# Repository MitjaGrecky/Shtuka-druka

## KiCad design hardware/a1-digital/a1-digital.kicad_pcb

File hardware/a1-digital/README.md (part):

# A1 - Digital audio board (under the slope, left; mates R1 at a right angle)

> *Outdated as a heading (audit 26.11.2026): current rev 1.1, see Status below and the Rev sections at the end; the rev 0.6 block is history.*
>
> **Rev 0.6 (18.11.2026, решение главного инженера, P108):** конденсаторы связи — по одному неполярному Würth WCAP-ASNP 865250349007 (47 мкФ 16 В, Ø8×6,5, LCSC C5530373) на канал, 40 шт., паять вручную (на JLC нет в наличии, Digikey 239 шт.). THD+N на 20–100 Гц замерить на первой плате. Rev 0.5 с парами FVH016 не заказывать.

20 differential ADC channels, 8 DAC channels, two XMOS xcore.ai, USB isolation, two clock sources, quiet supplies.
Plan, pinouts and sources: `PLAN.md`. Decisions: R82-R84 (two USB ports, TDM, 96 kHz hardware), R87 (volume in the DAC), R88 (two spare
channels), R114 (two oscillators), R116/R117 (converters, two paths per mic), R136 (CS4308P, current outputs).

**Status: rev 1.1 (25.11.2026) - placed board, not routed, pin rule (A-037) not yet applied; USB isolator TI ISOUSB211 since rev 0.9 (see the Rev sections at the end; rev 0.6 text below kept as history: 613 parts, 18.11.2026).** Schematic checked against the datasheets (cloud task #26, rev 0.2): CS4308P DS1317, CS53A04P DS1397
(same family as the CS5304P/8P - the CS5308P/CS5304P datasheets themselves were not reachable), XU316-1024-QF60B, ADuM4165/4166, SiTime/SCTF oscillators.

## Blocks

| Block | Parts | Notes |
|---|---|---|
| ADC | 2 x CS5308P (8 ch, C42457798) + 1 x CS5304P (4 ch, C49192888) | SPI software mode (CONFIG1 to VDD_A), ASP secondary, TDM out on DOUT1. Chip A = ADC 1-8 (mic 1-2 two paths, Hi-Z 1-2 two paths), B = ADC 9-16 (phono 2, line 1-6), C = ADC 17-20 (line 7-8, spare 1-2) |
| ADC input buffers | 20 x OPA1656 dual, 47 uF X5R (2.8 Hz) + 1.2k in, 300 R + 680 pF feedback, 10 R out, 15 nF across the pair | Cirrus circuit, gain 1/4: R1 delivers 8 Vrms diff FS -> 2 Vrms at the pins (AN0635); inverting, so the source P leg goes to the N pin (polarity kept); non-inverting inputs at ADC_VMID |
| DAC | CS4308P (8 ch) | Current outputs: 8 x OPA1656 dual I-V, Rf 1.2k + 620 pF per leg (AN0679), 47 R build-out, 1 nF across. Outputs 1-4 Main L/R, Aux L/R -> R1; 5-8 Phones 1 L/R, 2 L/R -> F1. Not in the EasyEDA library (R136) |
| xcore A (U) | XU316-1024-QF60B (C7397517), W25Q32JVSSIQ boot flash (4 MB, B18; C82344) | TDM master (BCLK, FSYNC, DAC data, 3 ADC data), SPI to the 4 converters (tile 1), converter reset, oscillator enables, USB port A from the R2 hub, XLINK0 to B |
| xcore B | XU316-1024-QF60B, W25Q16 | USB port B to the external computer through the ISOUSB211 (rev 0.9; was ADuM4166), PDM microphone (header), XLINK0 to A |
| USB isolator | TI ISOUSB211DPR (C5772877, rev 0.9; was ADuM4166 C5367256), USBLC6 on the computer side, Rd 5.1k | Computer side on the isolated ground GNDPC; the rear USB-C (PC) receptacle on the wall comes in over a JST PH 6 cable (R145: data only) |
| Clocks | 24.576 MHz and 22.5792 MHz oscillators with enable pins (parts to choose), 33 R each into MCLK, 22 R star to every load | Default 48 kHz family on; xcore A can switch (R114). 24 MHz crystals for both xcore cores |
| Supplies | +3V3A TPS7A4701 (ANY-OUT 3.3 V), +3V3D and +1V8 AP2112K, +0V9 x 2 TLV62568 (0.6 V x 1.5) from +5V; +-12 V from R1 for the op-amps | +-12 V and +5 V arrive through the R1 board-to-board connector (PW -> R1 -> A1) |

## Connectors

| J | To | Notes |
|---|---|---|
| 2x20 socket | R1 "to A1 (ADC 1-10)" | same pinout; pairs on adjacent pins with a GND pair between |
| 2x25 socket | R1 "to A1 (ADC 11-18, DAC 1-4, power)" | same pinout; +12V, -12V, +5V x 2 on pins 47-50 |
| 2x6 header | F1 "from A1" | Phones 1 and 2 pairs, twisted |
| JST PH 4 | R2 hub "USB down: A1 port A" | VBUS sense only |
| JST PH 6 | rear USB-C (PC) | PC_VBUS, DM, DP, CC1, CC2, GNDPC |
| JST PH 6 | spare ADC 19-20 | R88 |
| JST PH 6 x 2 | JTAG A and B (1.8 V logic) | xTAG adapter - check the pinout |
| JST PH 4 | PDM microphone | CLK, DATA, +3V3D, GND |

xcore pin plan (as in `gen/design.py`): A: MCLK X0D11, BCLK X0D00, FSYNC X0D35, DAC data X0D36, ADC data X0D37/38/39; SPI SCK X1D00,
MOSI X1D01, MISO X1D10, CS X1D11/X1D22/X1D13/X1D34; reset X0D29; oscillator enables X0D30/X0D31; hub VBUS sense X0D40; XLINK0 X1D16-X1D19.
B: MCLK X0D11, PDM X1D00/X1D01. QSPI boot on X0D01 (SS), X0D10 (SCLK), X0D04-07.

## Checked (cloud task #26, rev 0.2)

**Converters (CS4308P, CS53A04P family).** Pin maps of the CS4308P (all 48) and of the four-channel ADC half (supplies, SPI, ASP, CONFIG, IN1-4) agree with the schematic.
- Capacitors as in the typical-connection drawings: VDD_A1 and VDD_A2 each 4.7 uF + 10 nF, LDO_A_FILT 1 uF, LDO_D_FILT 1 uF with VDD_D tied to it (no separate cap),
  VDD_IO 0.1 uF. Rev 0.1 had 1 uF / 10 uF / 4.7 uF.
- DAC: DAC_FILTP 22 uF to **VDD_A2**, DAC_FILTN 22 uF to ground (rev 0.1: 4.7 uF between them), DAC_VMID 10 uF (rev 0.1: 1 uF).
  ADC: FILT 4.7 uF + 0.47 uF (the figure text is ambiguous between 0.47/4.7 and 0.22/2.2; VMID 2.2 uF + 0.22 uF), ADC_FILTP through 1 R to VDD_A.
- SPI mode: CONFIG1 0 R to VDD_A, **CONFIG5 to ground**; in software mode CONFIG2-4 of the ADC are the **HGC SPI outputs** (clock, data, chip select for external
  preamplifiers, off by default): 1 k to ground instead of 10 k. DAC CONFIG2-4 unused to ground.
- No power-up sequencing; RESET low >= 1 ms, control port ready 5 ms after the release; POR of VDD_A 1.9-2.7 V.
- MCLK 24.576 / 22.5792 MHz directly (software mode, PLL bypass) or 512 fs with the PLL, +-1 %, duty 40-60 %. **ASP secondary: MCLK, BCLK and FSYNC must come from a
  common source** - here MCLK from the oscillator and BCLK / FSYNC derived by xcore A from the same MCLK (lib_xua master mode does that).
- ADC input: 0 dBFS = 2.0 Vrms differential at the pins (scales with VDD_A), input resistance 3 kOhm differential in the default mode (INxx_HIZ = 0).
- **Coupling capacitors 68 uF -> 47 uF X5R 10 V (1210)**: a 68 uF 25 V ceramic does not exist, and a polarised one cannot be used - the buffer side sits at 1.6 V
  while each leg swings +-5.7 V at full scale (reverse voltage). Corner 2.8 Hz instead of 1.95 Hz; the capacitor voltage never exceeds 7.3 V. 20 x 2 = 40 pieces (rev 0.6: non-polar Würth WCAP-ASNP instead of X5R).
- CS4308P: **no LCSC number** (a new part; Digikey CS4308P-DNR, 16 weeks lead time, 48-QFN 6x6, 0.4 mm). Footprint body 6x6 and pitch 0.4 are confirmed;
  the exposed-pad size is in section 10 of the datasheet (not retrievable here) - draw the footprint from it. Output: 1.67 mA rms per channel, 1.2 kOhm = 2.0 Vrms (AN0679).

**XU316-1024-QF60B.**
- Pin map of the supplies and of all used ports agrees (VDD x 8 + paddles 61-64 at 0.9 V, VDDIOL/R/T 3.3 V, VDDIOB18 x 2 1.8 V, USB_VDD33 3.3 V, USB_VDD18 1.8 V).
  Bottom bank (XIN, XOUT, RST_N, JTAG) is 1.8 V only - correct.
- **PLL_AVDD:** 0.9 V nominal, filter = ferrite bead 600 R at 100 MHz (DCR < 1 R) + **1 uF** MLCC at the pin (rev 0.1: 4.7 uF + 100 nF kept as a second capacitor).
- **Sequencing:** VDD and VDDIO within about 50 ms, monotonic; the 3.3 V domains must be valid before reset is released, and VDDIOB18 must not be last - here all rails come from the
  same +5 V and the TLV62568 / AP2112K start together; RST_N has a 100 nF to ground with the 10 k pull-up to 1.8 V (about 1 ms delay), which keeps it low while the rails rise.
- Crystal 24 MHz, 12 pF load, ESR <= 60 R, tolerance +-500 ppm or better: C70590 with 18 pF caps is right.
- **USB PHY:** enable it on **tile 0** (xcore A and B). The USB ports of the PHY are not on the QF60 pins of tile 0; enabling it on **tile 1 removes ports 1F (X1D13) and 1K (X1D34) -
  our SPI chip selects CS_ADCC and CS_DAC of xcore A would be lost.** lib_xua then runs the USB and the audio on tile 0 (supported); the SPI to the converters and the PDM microphone stay on tile 1.
- Boot: X0D04-X0D06 are sampled after reset with weak pull-downs, 000 = QSPI; the flash must answer a Quad I/O read (0xEB) within 300 us, so its QE bit must be set (the first programming
  goes over JTAG with xflash, which sets it). A blank W25Q16 may pull IO2/IO3 up internally; if the board does not boot before the first programming, program it over JTAG.
- Flash: the datasheet gives no minimum; a lib_xua UAC2 application with DFU needs about 2x the image, so the user chose 4 MB (B18): W25Q32JVSSIQ (C82344), same package and pinout.
- Ports: BCLK X0D00 (1A), MCLK X0D11 (1D), FSYNC X0D35, DAC data X0D36, ADC data X0D37-39 are all 1-bit ports of tile 0 (nine 1-bit ports on tile 0: 1A, 1B, 1C, 1D, 1L-1P);
  SPI on tile 1 (1A, 1B, 1C, 1D, 1F, 1G, 1K). Everything the plan uses exists. TDM master with a 1-bit BCLK clock port is the lib_xua configuration; PDM needs a 1-bit data port (X1D01).

**ADuM4166** (pin table: all 20 agree).
- **VBUS2 was +5 V with VDD2 on the external 3.3 V: the internal LDO would fight our regulator** (and VDD1/VDD2 need exactly 0.1 uF with the LDO). Now VBUS2 = VDD2 = +3V3D (LDO bypassed, 3.0-3.6 V),
  VDD2 / VBUS2 0.1 uF, VDD1 0.1 uF (LDO output, **not** 1 uF: "above 0.1 uF disrupts the start-up"), VBUS1 0.1 uF; PGOOD open. VBUS1 = PC VBUS 3.0-5.5 V.
- Crystal 24 MHz, <= 50 ppm and <= 100 ppm stability, starts within 0.3 ms, typical load 10 pF: C70590 (12 pF) with 15 pF caps (about 10.5 pF) works; a 10 pF part is better. *(Outdated, P122: this is the ADuM4166 isolator crystal, gone in rev 0.9; the xcore crystal X322524MOB4SI uses 18 pF caps per the generator.)* Or a 24 MHz clock into XI2 (XO2 open).
- Footprint: LCSC lists it as SOIC-20-300mil (rev 0.1 had a 15.4 mm body "per the LCSC part" - a 300-mil SOIC-20 is 12.8 mm): check against the datasheet drawing; the LCSC number of the BRIZ-RL
  is C5581725 (out of stock on 14.11.2026, $15), the schematic carries C5367256 from the PC - check which one is the stocked variant.

**Oscillators** (R114; actual parts by the generator, P122): Y1 24.576 MHz SCTF SX3M24.576B10F20TNN (C7431342), Y2 22.5792 MHz SCTF SX3M22.5792B10F20TNN (C7431341), both 3.3 V CMOS, +-10 ppm, pin 1 tri-state; SiTime SiT8208AI-21-33E-24.576000 (C839665, 0.5 ps; **out of stock** on 14.11) is only the spare (В19). Earlier text (rev 0.2-0.5; SX3M22.5792M20F30TNN C2901572 and SiT8208 as the main part are outdated): Pin 1 = enable, high = on, as the schematic assumes. For a 123 dB ADC the clock jitter matters: SiTime
has 0.5 ps; the SCTF part must be checked or replaced (SiT8208 22.5792). *(Outdated, P122: SX3M is the accepted main part, SiT8208 is the spare; jitter is measured on the first board, B19.)* The 33 R + 22 R star is kept.

**Supplies.** TPS7A4701: ANY-OUT 1.4 + 1.6 + 0.2 + 0.1 = 3.3 V with pins 8 (1.6 V), 11 (0.2 V), 12 (0.1 V) to ground - confirmed from the symbol; NR/SS 1 uF not verified (TI text not retrievable).
AP2112K 3.3 V: 600 mA max, estimated 150 mA typical -> 0.26 W in a SOT-23-5 (250 K/W = +65 K): **warm, keep an eye on it on the first board** - the analog side is not on this regulator
(it is on the TPS7A4701). TLV62568 0.9 V x 2: 1 A, the feedback 0.6 x (1 + 100k / 200k) = 0.9 V is right; the xcore.ai core draws about 0.5 A at full load (to measure).

## Still open

- CS5308P and CS5304P datasheets (pins 12-22 of the CS5304P are DNC in the CS53A04P; the CS5308P has pins 13-22 as IN5-8 and the second VMID/FILT) - compare once the datasheet is available.
- Exposed-pad size of the CS4308P footprint; body length of the ADuM4166; CS4308P order.
- Oscillator parts (stock), 10 pF crystal for the ADuM4166.
- AP2112K temperature.

Checks: `tools/sch_netcheck.py hardware/a1-digital` - 663 symbol units, 1887 pins, 0 mismatches; every symbol pin listed. ERC by CI.
Symbols for the CS5308P / CS5304P / CS4308P / XU316 / ADuM4166: `hardware/common/gen/ic_symbols.py` -> `ShtukaDruka.kicad_sym`; footprint of
the XU316: `ShtukaDruka.pretty` (converted from the LCSC library with `tools/eda/lcsc_fp.py`).

Generators: `gen/design.py`, `gen/make_sch.py`. On the PC set `KICAD_SYMBOL_DIR=<repo>/hardware/common/sym7`.

License: CERN-OHL-S-2.0 (hardware), AGPL-3.0-or-later (scripts).

## Rev 0.3: placed board for routing (14.11.2026, PC)
Placed board (no routing) generated by `gen/make_pcb.py`; `UNROUTED` marker for CI; package `hardware/for-routing/A1`. Placement is a starting point: the rest by `hardware/common/gen/autoplace.py` (ICs on a grid, small parts around the IC they share signals with, cable headers along the bottom edge). Outline and mounting holes are rough until the enclosure is fixed. `pcb_geomcheck`: 0 problems.

Low case (17.11.2026, R162): the board stands on a 2 mm tray over the battery. Parts on the bottom side reach 7.7 mm (5 x CP 6.3 x 7.7), so the standoffs between the board and the tray must be >= 8.5 mm, with an insulating film on the tray. Socket rows of J1 / J2 end up about 30.4 / 32.9 mm above the floor (superseded: A1 now stands on the floor, R174; header height of R1 J4 / J5: R1 rev 0.7).

Rev 0.5 (17.11.2026, R172): 80 x FVH016 electrolytics in back-to-back pairs instead of the X5R capacitors; **superseded by rev 0.6 (P108), do not order rev 0.5**: the reverse-voltage rating of the pair was never confirmed (up to about +-2.8 V on each capacitor at 20 Hz and full scale).

Rev 0.6 (18.11.2026): 80 FVH016 заменены 40 одиночными WCAP-ASNP (47 мкФ, угол ≈ 2,8 Гц с 1,2 к). 613 деталей, 0 несовпадений нетлиста, 0 перекрытий. Footprint CP_Elec_8x6.5 приблизителен к даташиту.

## Rev 0.5: ADC overload clamps (audit 18.11.2026)
CS5308P DS1314F2 table 3-3: analog inputs -0.3 ... VDD_A + 0.3 V, +-10 mA. A clipped R1 stage leaves the buffer at -1.1 ... +4.4 V (about 70 mA through 10 R into the ADC diodes). One **BAT54S** (onsemi C19726, Schottky pair to +3V3A / GND) per ADC pin: 40 parts, near the pins. Stock: the CS5308P itself has 0 pcs at JLC on 18.11.2026 (Digikey or direct from Cirrus).

## Rev 0.6: 24.576 MHz oscillator (18.11.2026)
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
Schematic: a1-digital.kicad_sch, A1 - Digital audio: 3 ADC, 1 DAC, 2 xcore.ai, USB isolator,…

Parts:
C1, C3, C5, C22, C23, C37, C38, C52, C53, C203, C204, C258, C274: 1u; C_0603_1608Metric
C2, C4, C28, C30, C43, C45, C56: 2.2u; C_0603_1608Metric
C6, C9, C12, C207: 10u; C_0805_2012Metric
C7, C10, C11, C13, C14, C205, C206: 22u; C_0805_2012Metric
C8, C15, C16, C21, C36, C51, C202, C248, C249, C250, C251, C253, C254, C255, C256, C257, C259, C262, C263, C264, C265, C266, C267, C269, C270, C271, C272, C273, C275, C278, C279, C281, C283, C286, C288: 100n; C_0402_1005Metric
C17, C19, C24, C26, C32, C34, C39, C41, C47, C49, C54, C198, C200: 4.7u; C_0805_2012Metric
C18, C20, C33, C35, C48, C50, C199, C201, C284, C289: 10n; C_0402_1005Metric
C25, C27, C40, C42, C55: 470n; C_0402_1005Metric
C29, C31, C44, C46, C57: 220n; C_0402_1005Metric
C58, C59, C65, C66, C72, C73, C79, C80, C86, C87, C93, C94, C100, C101, C107, C108, C114, C115, C121, C122, C128, C129, C135, C136, C142, C143, C149, C150, C156, C157, C163, C164, C170, C171, C177, C178, C184, C185, C191, C192, C208, C209, C213, C214, C218, C219, C223, C224, C228, C229, C233, C234, C238, C239, C243, C244: 100n 25V; C_0603_1608Metric
C60, C62, C67, C69, C74, C76, C81, C83, C88, C90, C95, C97, C102, C104, C109, C111, C116, C118, C123, C125, C130, C132, C137, C139, C144, C146, C151, C153, C158, C160, C165, C167, C172, C174, C179, C181, C186, C188, C193, C195: 47u 16V NP; CP_Elec_8x6.5; LCSC C5530373
C61, C63, C68, C70, C75, C77, C82, C84, C89, C91, C96, C98, C103, C105, C110, C112, C117, C119, C124, C126, C131, C133, C138, C140, C145, C147, C152, C154, C159, C161, C166, C168, C173, C175, C180, C182, C187, C189, C194, C196: 680p C0G; C_0603_1608Metric
C64, C71, C78, C85, C92, C99, C106, C113, C120, C127, C134, C141, C148, C155, C162, C169, C176, C183, C190, C197: 15n C0G; C_0603_1608Metric
C210, C211, C215, C216, C220, C221, C225, C226, C230, C231, C235, C236, C240, C241, C245, C246: 620p C0G; C_0603_1608Metric
C212, C217, C222, C227, C232, C237, C242, C247: 1n C0G; C_0603_1608Metric
C252, C268: 4.7u; C_0603_1608Metric
C260, C261, C276, C277: 18p; C_0402_1005Metric
C280, C285: 1u; C_0402_1005Metric
C282, C287: 2.2u; C_0402_1005Metric
C290, C291, C292, C293, C294: 47u 25V; CP_Elec_6.3x7.7; LCSC C190223
D1, D2, D3, D4, D5, D6, D7, D8, D9, D10, D11, D12, D13, D14, D15, D16, D17, D18, D19, D20, D21, D22, D23, D24, D25, D26, D27, D28, D29, D30, D31, D32, D33, D34, D35, D36, D37, D38, D39, D40: BAT54S; SOT-23; LCSC C19726
FB1, FB2: 600R; R_0603_1608Metric; LCSC C14709
H1, H2, H3, H4, H5, H6: M3; MountingHole_3.2mm_M3_ISO7380
J1: from R1 (ADC 1-10); PinSocket_2x20_P2.54mm_Horizontal
J2: R1 (ADC 11-18, DAC 1-4, power); PinSocket_2x25_P2.54mm_Horizontal
J3: to F1; PinHeader_2x06_P2.54mm_Vertical
J4: USB port A (hub); JST_PH_B4B-PH-K_1x04_P2.00mm_Vertical; LCSC C131334
J5: USB-C PC; JST_PH_B6B-PH-K_1x06_P2.00mm_Vertical; LCSC C131342
J6: spare ADC 19-20; JST_PH_B6B-PH-K_1x06_P2.00mm_Vertical; LCSC C131342
J7: PDM mic; JST_PH_B4B-PH-K_1x04_P2.00mm_Vertical; LCSC C131334
J8: JTAG A; JST_PH_B6B-PH-K_1x06_P2.00mm_Vertical; LCSC C131342
J9: JTAG B; JST_PH_B6B-PH-K_1x06_P2.00mm_Vertical; LCSC C131342
L1, L2: 2.2uH; L_Bourns-SRN4018
R1, R3, R10, R20, R30, R44, R45, R52, R53, R60, R61, R68, R69, R76, R77, R84, R85, R92, R93, R100, R101, R108, R109, R116, R117, R124, R125, R132, R133, R140, R141, R148, R149, R156, R157, R164, R165, R172, R173, R180, R181, R188, R189, R196, R197, R199, R250, R251, R252, R253, R254, R255, R256: 100k; R_0402_1005Metric
R2, R4: 200k; R_0402_1005Metric
R5, R7, R16, R26, R36, R202, R203, R204, R205, R239, R240, R242, R243, R244: 10k; R_0402_1005Metric
R6, R8, R11, R21, R31, R200: 33; R_0402_1005Metric
R9, R19, R29, R198, R238, R241, R248, R249: 22; R_0402_1005Metric
R12, R22, R32, R201: 0; R_0402_1005Metric
R13, R14, R15, R23, R24, R25, R33, R34, R35: 1k; R_0402_1005Metric
R17, R18, R27, R28, R37: 1; R_0402_1005Metric
R38, R41, R46, R49, R54, R57, R62, R65, R70, R73, R78, R81, R86, R89, R94, R97, R102, R105, R110, R113, R118, R121, R126, R129, R134, R137, R142, R145, R150, R153, R158, R161, R166, R169, R174, R177, R182, R185, R190, R193, R206, R208, R210, R212, R214, R216, R218, R220, R222, R224, R226, R228, R230, R232, R234, R236: 1.2k; R_0402_1005Metric
R39, R42, R47, R50, R55, R58, R63, R66, R71, R74, R79, R82, R87, R90, R95, R98, R103, R106, R111, R114, R119, R122, R127, R130, R135, R138, R143, R146, R151, R154, R159, R162, R167, R170, R175, R178, R183, R186, R191, R194: 300; R_0402_1005Metric
R40, R43, R48, R51, R56, R59, R64, R67, R72, R75, R80, R83, R88, R91, R96, R99, R104, R107, R112, R115, R120, R123, R128, R131, R136, R139, R144, R147, R152, R155, R160, R163, R168, R171, R176, R179, R184, R187, R192, R195: 10; R_0402_1005Metric
R207, R209, R211, R213, R215, R217, R219, R221, R223, R225, R227, R229, R231, R233, R235, R237: 47; R_0603_1608Metric
R245: 20k; R_0402_1005Metric
R246, R247: 5.1k; R_0402_1005Metric
U1: AP2112K-3.3; SOT-23-5; LCSC C51118
U2: AP2112K-1.8; SOT-23-5; LCSC C176944
U3: TPS7A4701; Texas_RGW0020A_VQFN-20-1EP_5x5mm_P0.65mm_EP3.15x3.15mm_Ther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; LCSC C90084
U4, U5: TLV62568; SOT-23-5; LCSC C163219
U6, U7: CS5308P; QFN-48-1EP_6x6mm_P0.4mm_EP4.6x4.6mm; LCSC C42457798
U8: CS5304P; QFN-48-1EP_6x6mm_P0.4mm_EP4.6x4.6mm; LCSC C49192888
U9, U10, U11, U12, U13, U14, U15, U16, U17, U18, U19, U20, U21, U22, U23, U24, U25, U26, U27, U28, U30, U31, U32, U33, U34, U35, U36, U37: OPA1656; SOIC-8_3.9x4.9mm_P1.27mm; LCSC C1849431
U29: CS4308P; QFN-48-1EP_6x6mm_P0.4mm_EP4.3x4.3mm
U38, U39: XU316-1024-QF60B; XU316-1024-QF60B_QFN-60_7x7_P0.4; LCSC C7397517
U40, U41: W25Q32JVSSIQ; SOIC-8_5.3x5.3mm_P1.27mm; LCSC C179173
U42, U43: USBLC6-2SC6; SOT-23-6; LCSC C7519
U44: ISOUSB211DPR; SSOP-28_DP0028A_7.5x10.3mm_P0.65mm; LCSC C5772877
Y1: 24.576MHz; Oscillator_SMD_Abracon_ASE-4Pin_3.2x2.5mm; LCSC C7431342
Y2: 22.5792MHz; Oscillator_SMD_Abracon_ASE-4Pin_3.2x2.5mm; LCSC C7431341
Y3, Y4: 24MHz; Crystal_SMD_3225-4Pin_3.2x2.5mm; LCSC C70590

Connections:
+5V: C1.1, C3.1, C6.1, C9.1, C12.1, C294.1, J2.49, J2.50, U1.1 (VIN), U1.3 (EN), U2.1 (VIN), U2.3 (EN), U3.13 (EN), U3.15 (IN), U3.16 (IN), U4.1 (EN), U4.4 (VIN), U5.1 (EN), U5.4 (VIN)
/+0V9A: C10.1, C11.1, C248.1, C249.1, C250.1, C251.1, C252.1, FB1.1, L1.2, R1.1, U38.4 (VDD), U38.12 (VDD), U38.19 (VDD), U38.27 (VDD), U38.34 (VDD), U38.42 (VDD), U38.49 (VDD), U38.57 (VDD), U38.61 (VDD), U38.62 (VDD), U38.63 (VDD), U38.64 (VDD)
/+0V9B: C13.1, C14.1, C264.1, C265.1, C266.1, C267.1, C268.1, FB2.1, L2.2, R3.1, U39.4 (VDD), U39.12 (VDD), U39.19 (VDD), U39.27 (VDD), U39.34 (VDD), U39.42 (VDD), U39.49 (VDD), U39.57 (VDD), U39.61 (VDD), U39.62 (VDD), U39.63 (VDD), U39.64 (VDD)
/+1V8: C4.1, C256.1, C257.1, C272.1, C273.1, C287.1, C288.1, C289.1, R239.2, R242.2, U2.5 (VOUT), U38.17 (VDDIOB18), U38.26 (VDDIOB18), U38.31 (USB_VDD18), U39.17 (VDDIOB18), U39.26 (VDDIOB18), U39.31 (USB_VDD18), U44.18 (V1P8V2), U44.24 (VCC2), U44.25 (V1P8V2)
/+3V3A: C7.1, C8.1, C17.1, C18.1, C19.1, C20.1, C32.1, C33.1, C34.1, C35.1, C47.1, C48.1, C49.1, C50.1, C198.1, C199.1, C200.1, C201.1, C205.2, D1.2 (K), D2.2 (K), D3.2 (K), D4.2 (K), D5.2 (K), D6.2 (K), D7.2 (K), D8.2 (K), D9.2 (K), D10.2 (K), D11.2 (K), D12.2 (K), D13.2 (K), D14.2 (K), D15.2 (K), D16.2 (K), D17.2 (K), D18.2 (K), D19.2 (K), D20.2 (K), D21.2 (K), D22.2 (K), D23.2 (K), D24.2 (K), D25.2 (K), D26.2 (K), D27.2 (K), D28.2 (K), D29.2 (K), D30.2 (K), D31.2 (K), D32.2 (K), D33.2 (K), D34.2 (K), D35.2 (K), D36.2 (K), D37.2 (K), D38.2 (K), D39.2 (K), D40.2 (K), R12.2, R17.1, R18.1, R22.2, R27.1, R28.1, R32.2, R37.1, R201.2, U3.1 (OUT), U3.3 (SENSE/FB), U3.20 (OUT), U6.5 (VDD_A1), U6.9 (VDD_A2), U7.5 (VDD_A1), U7.9 (VDD_A2), U8.5 (VDD_A1), U8.9 (VDD_A2), U29.2 (VDD_A1), U29.38 (VDD_A2)
/+3V3D: C2.1, C15.1, C16.1, C21.1, C36.1, C51.1, C202.1, C253.1, C254.1, C255.1, C263.1, C269.1, C270.1, C271.1, C279.1, C285.1, C286.1, J7.3, R5.2, R240.2, R243.2, R253.2, R254.2, R255.2, R256.2, U1.5 (VOUT), U6.31 (VDD_IO), U7.31 (VDD_IO), U8.31 (VDD_IO), U29.11 (VDD_IO), U38.8 (VDDIOL), U38.30 (USB_VDD33), U38.38 (VDDIOR), U38.52 (VDDIOT), U39.8 (VDDIOL), U39.30 (USB_VDD33), U39.38 (VDDIOR), U39.52 (VDDIOT), U40.8 (VCC), U41.8 (VCC), U44.16 (CDPENZ2), U44.27 (V3P3V2), U44.28 (VBUS2), Y1.4 (Vdd), Y2.4 (Vdd)
/+12V: C58.1, C65.1, C72.1, C79.1, C86.1, C93.1, C100.1, C107.1, C114.1, C121.1, C128.1, C135.1, C142.1, C149.1, C156.1, C163.1, C170.1, C177.1, C184.1, C191.1, C208.1, C213.1, C218.1, C223.1, C228.1, C233.1, C238.1, C243.1, C290.1, C292.1, J2.47, U9.8 (V+), U10.8 (V+), U11.8 (V+), U12.8 (V+), U13.8 (V+), U14.8 (V+), U15.8 (V+), U16.8 (V+), U17.8 (V+), U18.8 (V+), U19.8 (V+), U20.8 (V+), U21.8 (V+), U22.8 (V+), U23.8 (V+), U24.8 (V+), U25.8 (V+), U26.8 (V+), U27.8 (V+), U28.8 (V+), U30.8 (V+), U31.8 (V+), U32.8 (V+), U33.8 (V+), U34.8 (V+), U35.8 (V+), U36.8 (V+), U37.8 (V+)
/-12V: C59.1, C66.1, C73.1, C80.1, C87.1, C94.1, C101.1, C108.1, C115.1, C122.1, C129.1, C136.1, C143.1, C150.1, C157.1, C164.1, C171.1, C178.1, C185.1, C192.1, C209.1, C214.1, C219.1, C224.1, C229.1, C234.1, C239.1, C244.1, C291.2, C293.2, J2.48, U9.4 (V-), U10.4 (V-), U11.4 (V-), U12.4 (V-), U13.4 (V-), U14.4 (V-), U15.4 (V-), U16.4 (V-), U17.4 (V-), U18.4 (V-), U19.4 (V-), U20.4 (V-), U21.4 (V-), U22.4 (V-), U23.4 (V-), U24.4 (V-), U25.4 (V-), U26.4 (V-), U27.4 (V-), U28.4 (V-), U30.4 (V-), U31.4 (V-), U32.4 (V-), U33.4 (V-), U34.4 (V-), U35.4 (V-), U36.4 (V-), U37.4 (V-)
/ADC1_BN: C64.2, D1.3 (COM), R40.2, U6.39 (IN1N)
/ADC1_BP: C64.1, D2.3 (COM), R43.2, U6.40 (IN1P)
/ADC1_N: C62.1, J1.2
/ADC1_P: C60.1, J1.1
/ADC2_BN: C71.2, D3.3 (COM), R48.2, U6.41 (IN2N)
/ADC2_BP: C71.1, D4.3 (COM), R51.2, U6.42 (IN2P)
/ADC2_N: C69.1, J1.6
/ADC2_P: C67.1, J1.5
/ADC3_BN: C78.2, D5.3 (COM), R56.2, U6.45 (IN3N)
/ADC3_BP: C78.1, D6.3 (COM), R59.2, U6.46 (IN3P)
/ADC3_N: C76.1, J1.10
/ADC3_P: C74.1, J1.9
/ADC4_BN: C85.2, D7.3 (COM), R64.2, U6.47 (IN4N)
/ADC4_BP: C85.1, D8.3 (COM), R67.2, U6.48 (IN4P)
/ADC4_N: C83.1, J1.14
/ADC4_P: C81.1, J1.13
/ADC5_BN: C92.2, D9.3 (COM), R72.2, U6.13 (IN5N)
/ADC5_BP: C92.1, D10.3 (COM), R75.2, U6.14 (IN5P)
/ADC5_N: C90.1, J1.18
/ADC5_P: C88.1, J1.17
/ADC6_BN: C99.2, D11.3 (COM), R80.2, U6.15 (IN6N)
/ADC6_BP: C99.1, D12.3 (COM), R83.2, U6.16 (IN6P)
/ADC6_N: C97.1, J1.22
/ADC6_P: C95.1, J1.21
/ADC7_BN: C106.2, D13.3 (COM), R88.2, U6.19 (IN7N)
/ADC7_BP: C106.1, D14.3 (COM), R91.2, U6.20 (IN7P)
/ADC7_N: C104.1, J1.26
/ADC7_P: C102.1, J1.25
/ADC8_BN: C113.2, D15.3 (COM), R96.2, U6.21 (IN8N)
/ADC8_BP: C113.1, D16.3 (COM), R99.2, U6.22 (IN8P)
/ADC8_N: C111.1, J1.30
/ADC8_P: C109.1, J1.29
/ADC9_BN: C120.2, D17.3 (COM), R104.2, U7.39 (IN1N)
/ADC9_BP: C120.1, D18.3 (COM), R107.2, U7.40 (IN1P)
/ADC9_N: C118.1, J1.34
/ADC9_P: C116.1, J1.33
/ADC10_BN: C127.2, D19.3 (COM), R112.2, U7.41 (IN2N)
/ADC10_BP: C127.1, D20.3 (COM), R115.2, U7.42 (IN2P)
/ADC10_N: C125.1, J1.38
/ADC10_P: C123.1, J1.37
/ADC11_BN: C134.2, D21.3 (COM), R120.2, U7.45 (IN3N)
/ADC11_BP: C134.1, D22.3 (COM), R123.2, U7.46 (IN3P)
/ADC11_N: C132.1, J2.2
/ADC11_P: C130.1, J2.1
/ADC12_BN: C141.2, D23.3 (COM), R128.2, U7.47 (IN4N)
/ADC12_BP: C141.1, D24.3 (COM), R131.2, U7.48 (IN4P)
/ADC12_N: C139.1, J2.6
/ADC12_P: C137.1, J2.5
/ADC13_BN: C148.2, D25.3 (COM), R136.2, U7.13 (IN5N)
/ADC13_BP: C148.1, D26.3 (COM), R139.2, U7.14 (IN5P)
/ADC13_N: C146.1, J2.10
/ADC13_P: C144.1, J2.9
/ADC14_BN: C155.2, D27.3 (COM), R144.2, U7.15 (IN6N)
/ADC14_BP: C155.1, D28.3 (COM), R147.2, U7.16 (IN6P)
/ADC14_N: C153.1, J2.14
/ADC14_P: C151.1, J2.13
/ADC15_BN: C162.2, D29.3 (COM), R152.2, U7.19 (IN7N)
/ADC15_BP: C162.1, D30.3 (COM), R155.2, U7.20 (IN7P)
/ADC15_N: C160.1, J2.18
/ADC15_P: C158.1, J2.17
/ADC16_BN: C169.2, D31.3 (COM), R160.2, U7.21 (IN8N)
/ADC16_BP: C169.1, D32.3 (COM), R163.2, U7.22 (IN8P)
/ADC16_N: C167.1, J2.22
/ADC16_P: C165.1, J2.21
/ADC17_BN: C176.2, D33.3 (COM), R168.2, U8.39 (IN1N)
/ADC17_BP: C176.1, D34.3 (COM), R171.2, U8.40 (IN1P)
/ADC17_N: C174.1, J2.26
/ADC17_P: C172.1, J2.25
/ADC18_BN: C183.2, D35.3 (COM), R176.2, U8.41 (IN2N)
/ADC18_BP: C183.1, D36.3 (COM), R179.2, U8.42 (IN2P)
/ADC18_N: C181.1, J2.30
/ADC18_P: C179.1, J2.29
/ADC19_BN: C190.2, D37.3 (COM), R184.2, U8.45 (IN3N)
/ADC19_BP: C190.1, D38.3 (COM), R187.2, U8.46 (IN3P)
/ADC19_N: C188.1, J6.2
/ADC19_P: C186.1, J6.1
/ADC20_BN: C197.2, D39.3 (COM), R192.2, U8.47 (IN4N)
/ADC20_BP: C197.1, D40.3 (COM), R195.2, U8.48 (IN4P)
/ADC20_N: C195.1, J6.5
/ADC20_P: C193.1, J6.4
/ADCA_CFG1: R12.1, U6.2 (CONFIG1)
/ADCA_CFG2: R13.1, U6.3 (CONFIG2/HGC_SCK)
/ADCA_CFG3: R14.1, U6.4 (CONFIG3/HGC_SDO)
/ADCA_CFG4: R15.1, U6.10 (CONFIG4/HGC_CS)
/ADCA_CFG5: R16.1, U6.11 (CONFIG5)
/ADCA_F1N: C24.2, C25.2, U6.44 (ADC_FILT1N)
/ADCA_F1P: C24.1, C25.1, R17.2, U6.43 (ADC_FILT1P)
/ADCA_F2N: C26.2, C27.2, U6.17 (ADC_FILT2N)
/ADCA_F2P: C26.1, C27.1, R18.2, U6.18 (ADC_FILT2P)
/ADCA_LDOA: C23.1, U6.7 (LDO_A_FILT)
/ADCA_LDOD: C22.1, U6.32 (LDO_D_FILT), U6.33 (VDD_D)
/ADCA_SDO: U6.25 (ASP_DOUT1), U38.44 (X0D37)
/ADCA_VMID1: C28.1, C29.1, U6.1 (ADC_VMID1), U9.3 (+), U9.5 (+), U10.3 (+), U10.5 (+), U11.3 (+), U11.5 (+), U12.3 (+), U12.5 (+)
/ADCA_VMID2: C30.1, C31.1, U6.12 (ADC_VMID2), U13.3 (+), U13.5 (+), U14.3 (+), U14.5 (+), U15.3 (+), U15.5 (+), U16.3 (+), U16.5 (+)
/ADCB_CFG1: R22.1, U7.2 (CONFIG1)
/ADCB_CFG2: R23.1, U7.3 (CONFIG2/HGC_SCK)
/ADCB_CFG3: R24.1, U7.4 (CONFIG3/HGC_SDO)
/ADCB_CFG4: R25.1, U7.10 (CONFIG4/HGC_CS)
/ADCB_CFG5: R26.1, U7.11 (CONFIG5)
/ADCB_F1N: C39.2, C40.2, U7.44 (ADC_FILT1N)
/ADCB_F1P: C39.1, C40.1, R27.2, U7.43 (ADC_FILT1P)
/ADCB_F2N: C41.2, C42.2, U7.17 (ADC_FILT2N)
/ADCB_F2P: C41.1, C42.1, R28.2, U7.18 (ADC_FILT2P)
/ADCB_LDOA: C38.1, U7.7 (LDO_A_FILT)
/ADCB_LDOD: C37.1, U7.32 (LDO_D_FILT), U7.33 (VDD_D)
/ADCB_SDO: U7.25 (ASP_DOUT1), U38.45 (X0D38)
/ADCB_VMID1: C43.1, C44.1, U7.1 (ADC_VMID1), U17.3 (+), U17.5 (+), U18.3 (+), U18.5 (+), U19.3 (+), U19.5 (+), U20.3 (+), U20.5 (+)
/ADCB_VMID2: C45.1, C46.1, U7.12 (ADC_VMID2), U21.3 (+), U21.5 (+), U22.3 (+), U22.5 (+), U23.3 (+), U23.5 (+), U24.3 (+), U24.5 (+)
/ADCC_CFG1: R32.1, U8.2 (CONFIG1)
/ADCC_CFG2: R33.1, U8.3 (CONFIG2/HGC_SCK)
/ADCC_CFG3: R34.1, U8.4 (CONFIG3/HGC_SDO)
/ADCC_CFG4: R35.1, U8.10 (CONFIG4/HGC_CS)
/ADCC_CFG5: R36.1, U8.11 (CONFIG5)
/ADCC_F1N: C54.2, C55.2, U8.44 (ADC_FILTN)
/ADCC_F1P: C54.1, C55.1, R37.2, U8.43 (ADC_FILTP)
/ADCC_LDOA: C53.1, U8.7 (LDO_A_FILT)
/ADCC_LDOD: C52.1, U8.32 (LDO_D_FILT), U8.33 (VDD_D)
/ADCC_SDO: U8.25 (ASP_DOUT1), U38.47 (X0D39)
/ADCC_VMID: C56.1, C57.1, U8.1 (ADC_VMID), U25.3 (+), U25.5 (+), U26.3 (+), U26.5 (+), U27.3 (+), U27.5 (+), U28.3 (+), U28.5 (+)
/B1_CA: C60.2, R38.1, R44.1
/B1_CB: C62.2, R41.1, R45.1
/B1_IA: C61.2, R38.2, R39.2, U9.2 (-)
/B1_IB: C63.2, R41.2, R42.2, U9.6 (-)
/B1_OA: C61.1, R39.1, R40.1, U9.1
/B1_OB: C63.1, R42.1, R43.1, U9.7
/B2_CA: C67.2, R46.1, R52.1
/B2_CB: C69.2, R49.1, R53.1
/B2_IA: C68.2, R46.2, R47.2, U10.2 (-)
/B2_IB: C70.2, R49.2, R50.2, U10.6 (-)
/B2_OA: C68.1, R47.1, R48.1, U10.1
/B2_OB: C70.1, R50.1, R51.1, U10.7
/B3_CA: C74.2, R54.1, R60.1
/B3_CB: C76.2, R57.1, R61.1
/B3_IA: C75.2, R54.2, R55.2, U11.2 (-)
/B3_IB: C77.2, R57.2, R58.2, U11.6 (-)
/B3_OA: C75.1, R55.1, R56.1, U11.1
/B3_OB: C77.1, R58.1, R59.1, U11.7
/B4_CA: C81.2, R62.1, R68.1
/B4_CB: C83.2, R65.1, R69.1
/B4_IA: C82.2, R62.2, R63.2, U12.2 (-)
/B4_IB: C84.2, R65.2, R66.2, U12.6 (-)
/B4_OA: C82.1, R63.1, R64.1, U12.1
/B4_OB: C84.1, R66.1, R67.1, U12.7
/B5_CA: C88.2, R70.1, R76.1
/B5_CB: C90.2, R73.1, R77.1
/B5_IA: C89.2, R70.2, R71.2, U13.2 (-)
/B5_IB: C91.2, R73.2, R74.2, U13.6 (-)
/B5_OA: C89.1, R71.1, R72.1, U13.1
/B5_OB: C91.1, R74.1, R75.1, U13.7
/B6_CA: C95.2, R78.1, R84.1
/B6_CB: C97.2, R81.1, R85.1
/B6_IA: C96.2, R78.2, R79.2, U14.2 (-)
/B6_IB: C98.2, R81.2, R82.2, U14.6 (-)
/B6_OA: C96.1, R79.1, R80.1, U14.1
/B6_OB: C98.1, R82.1, R83.1, U14.7
/B7_CA: C102.2, R86.1, R92.1
/B7_CB: C104.2, R89.1, R93.1
/B7_IA: C103.2, R86.2, R87.2, U15.2 (-)
/B7_IB: C105.2, R89.2, R90.2, U15.6 (-)
/B7_OA: C103.1, R87.1, R88.1, U15.1
/B7_OB: C105.1, R90.1, R91.1, U15.7
/B8_CA: C109.2, R94.1, R100.1
/B8_CB: C111.2, R97.1, R101.1
/B8_IA: C110.2, R94.2, R95.2, U16.2 (-)
/B8_IB: C112.2, R97.2, R98.2, U16.6 (-)
/B8_OA: C110.1, R95.1, R96.1, U16.1
/B8_OB: C112.1, R98.1, R99.1, U16.7
/B9_CA: C116.2, R102.1, R108.1
/B9_CB: C118.2, R105.1, R109.1
/B9_IA: C117.2, R102.2, R103.2, U17.2 (-)
/B9_IB: C119.2, R105.2, R106.2, U17.6 (-)
/B9_OA: C117.1, R103.1, R104.1, U17.1
/B9_OB: C119.1, R106.1, R107.1, U17.7
/B10_CA: C123.2, R110.1, R116.1
/B10_CB: C125.2, R113.1, R117.1
/B10_IA: C124.2, R110.2, R111.2, U18.2 (-)
/B10_IB: C126.2, R113.2, R114.2, U18.6 (-)
/B10_OA: C124.1, R111.1, R112.1, U18.1
/B10_OB: C126.1, R114.1, R115.1, U18.7
/B11_CA: C130.2, R118.1, R124.1
/B11_CB: C132.2, R121.1, R125.1
/B11_IA: C131.2, R118.2, R119.2, U19.2 (-)
/B11_IB: C133.2, R121.2, R122.2, U19.6 (-)
/B11_OA: C131.1, R119.1, R120.1, U19.1
/B11_OB: C133.1, R122.1, R123.1, U19.7
/B12_CA: C137.2, R126.1, R132.1
/B12_CB: C139.2, R129.1, R133.1
/B12_IA: C138.2, R126.2, R127.2, U20.2 (-)
/B12_IB: C140.2, R129.2, R130.2, U20.6 (-)
/B12_OA: C138.1, R127.1, R128.1, U20.1
/B12_OB: C140.1, R130.1, R131.1, U20.7
/B13_CA: C144.2, R134.1, R140.1
/B13_CB: C146.2, R137.1, R141.1
/B13_IA: C145.2, R134.2, R135.2, U21.2 (-)
/B13_IB: C147.2, R137.2, R138.2, U21.6 (-)
/B13_OA: C145.1, R135.1, R136.1, U21.1
/B13_OB: C147.1, R138.1, R139.1, U21.7
/B14_CA: C151.2, R142.1, R148.1
/B14_CB: C153.2, R145.1, R149.1
/B14_IA: C152.2, R142.2, R143.2, U22.2 (-)
/B14_IB: C154.2, R145.2, R146.2, U22.6 (-)
/B14_OA: C152.1, R143.1, R144.1, U22.1
/B14_OB: C154.1, R146.1, R147.1, U22.7
/B15_CA: C158.2, R150.1, R156.1
/B15_CB: C160.2, R153.1, R157.1
/B15_IA: C159.2, R150.2, R151.2, U23.2 (-)
/B15_IB: C161.2, R153.2, R154.2, U23.6 (-)
/B15_OA: C159.1, R151.1, R152.1, U23.1
/B15_OB: C161.1, R154.1, R155.1, U23.7
/B16_CA: C165.2, R158.1, R164.1
/B16_CB: C167.2, R161.1, R165.1
/B16_IA: C166.2, R158.2, R159.2, U24.2 (-)
/B16_IB: C168.2, R161.2, R162.2, U24.6 (-)
/B16_OA: C166.1, R159.1, R160.1, U24.1
/B16_OB: C168.1, R162.1, R163.1, U24.7
/B17_CA: C172.2, R166.1, R172.1
/B17_CB: C174.2, R169.1, R173.1
/B17_IA: C173.2, R166.2, R167.2, U25.2 (-)
/B17_IB: C175.2, R169.2, R170.2, U25.6 (-)
/B17_OA: C173.1, R167.1, R168.1, U25.1
/B17_OB: C175.1, R170.1, R171.1, U25.7
/B18_CA: C179.2, R174.1, R180.1
/B18_CB: C181.2, R177.1, R181.1
/B18_IA: C180.2, R174.2, R175.2, U26.2 (-)
/B18_IB: C182.2, R177.2, R178.2, U26.6 (-)
/B18_OA: C180.1, R175.1, R176.1, U26.1
/B18_OB: C182.1, R178.1, R179.1, U26.7
/B19_CA: C186.2, R182.1, R188.1
/B19_CB: C188.2, R185.1, R189.1
/B19_IA: C187.2, R182.2, R183.2, U27.2 (-)
/B19_IB: C189.2, R185.2, R186.2, U27.6 (-)
/B19_OA: C187.1, R183.1, R184.1, U27.1
/B19_OB: C189.1, R186.1, R187.1, U27.7
/B20_CA: C193.2, R190.1, R196.1
/B20_CB: C195.2, R193.1, R197.1
/B20_IA: C194.2, R190.2, R191.2, U28.2 (-)
/B20_IB: C196.2, R193.2, R194.2, U28.6 (-)
/B20_OA: C194.1, R191.1, R192.1, U28.1
/B20_OB: C196.1, R194.1, R195.1, U28.7
/BCLK: R248.2, U6.29 (ASP_BCLK), U7.29 (ASP_BCLK), U8.29 (ASP_BCLK), U29.9 (ASP_BCLK/DSD_CLK)
/BCLK_X: R248.1, U38.6 (X0D00)
/CONV_RESET: R11.1, R21.1, R31.1, R200.1, R251.1, U38.40 (X0D29)
/CS_ADCA: R253.1, U6.38 (SPI_CS), U38.14 (X1D11)
/CS_ADCB: R254.1, U7.38 (SPI_CS), U38.39 (X1D22)
/CS_ADCC: R255.1, U8.38 (SPI_CS), U38.32 (X1D13)
/CS_DAC: R256.1, U29.20 (SPI_CS), U38.53 (X1D34)
/DAC_AL_N: C222.2, J2.42, R217.2
/DAC_AL_P: C222.1, J2.41, R215.2
/DAC_AR_N: C227.2, J2.46, R221.2
/DAC_AR_P: C227.1, J2.45, R219.2
/DAC_CFG1: R201.1, U29.48 (CONFIG1)
/DAC_CFG2: R202.1, U29.22 (CONFIG2/DSD_DIN5)
/DAC_CFG3: R203.1, U29.21 (CONFIG3/DSD_DIN6)
/DAC_CFG4: R204.1, U29.23 (CONFIG4)
/DAC_CFG5: R205.1, U29.1 (CONFIG5)
/DAC_DIN: R250.1, U29.16 (ASP_DIN1/DSD_DIN1), U38.43 (X0D36)
/DAC_FN: C206.1, U29.40 (DAC_FILTN)
/DAC_FP: C205.1, U29.39 (DAC_FILTP)
/DAC_LDOA: C204.1, U29.4 (LDO_A_FILT)
/DAC_LDOD: C203.1, U29.6 (LDO_D_FILT), U29.7 (VDD_D)
/DAC_ML_N: C212.2, J2.34, R209.2
/DAC_ML_P: C212.1, J2.33, R207.2
/DAC_MR_N: C217.2, J2.38, R213.2
/DAC_MR_P: C217.1, J2.37, R211.2
/DAC_VMID: C207.1, U29.32 (DAC_VMID), U30.3 (+), U30.5 (+), U31.3 (+), U31.5 (+), U32.3 (+), U32.5 (+), U33.3 (+), U33.5 (+), U34.3 (+), U34.5 (+), U35.3 (+), U35.5 (+), U36.3 (+), U36.5 (+), U37.3 (+), U37.5 (+)
/DO1_N: C211.2, R208.2, U29.45 (OUT1N), U30.6 (-)
/DO1_P: C210.2, R206.2, U29.46 (OUT1P), U30.2 (-)
/DO1_VN: C211.1, R208.1, R209.1, U30.7
/DO1_VP: C210.1, R206.1, R207.1, U30.1
/DO2_N: C216.2, R212.2, U29.43 (OUT2N), U31.6 (-)
/DO2_P: C215.2, R210.2, U29.44 (OUT2P), U31.2 (-)
/DO2_VN: C216.1, R212.1, R213.1, U31.7
/DO2_VP: C215.1, R210.1, R211.1, U31.1
/DO3_N: C221.2, R216.2, U29.35 (OUT3N), U32.6 (-)
/DO3_P: C220.2, R214.2, U29.36 (OUT3P), U32.2 (-)
/DO3_VN: C221.1, R216.1, R217.1, U32.7
/DO3_VP: C220.1, R214.1, R215.1, U32.1
/DO4_N: C226.2, R220.2, U29.33 (OUT4N), U33.6 (-)
/DO4_P: C225.2, R218.2, U29.34 (OUT4P), U33.2 (-)
/DO4_VN: C226.1, R220.1, R221.1, U33.7
/DO4_VP: C225.1, R218.1, R219.1, U33.1
/DO5_N: C231.2, R224.2, U29.30 (OUT5N), U34.6 (-)
/DO5_P: C230.2, R222.2, U29.31 (OUT5P), U34.2 (-)
/DO5_VN: C231.1, R224.1, R225.1, U34.7
/DO5_VP: C230.1, R222.1, R223.1, U34.1
/DO6_N: C236.2, R228.2, U29.28 (OUT6N), U35.6 (-)
/DO6_P: C235.2, R226.2, U29.29 (OUT6P), U35.2 (-)
/DO6_VN: C236.1, R228.1, R229.1, U35.7
/DO6_VP: C235.1, R226.1, R227.1, U35.1
/DO7_N: C241.2, R232.2, U29.26 (OUT7N), U36.6 (-)
/DO7_P: C240.2, R230.2, U29.27 (OUT7P), U36.2 (-)
/DO7_VN: C241.1, R232.1, R233.1, U36.7
/DO7_VP: C240.1, R230.1, R231.1, U36.1
/DO8_N: C246.2, R236.2, U29.24 (OUT8N), U37.6 (-)
/DO8_P: C245.2, R234.2, U29.25 (OUT8P), U37.2 (-)
/DO8_VN: C246.1, R236.1, R237.1, U37.7
/DO8_VP: C245.1, R234.1, R235.1, U37.1
/FBA: R1.2, R2.1, U4.5 (FB)
/FBB: R3.2, R4.1, U5.5 (FB)
/FSYNC: R249.2, U6.24 (ASP_FSYNC), U7.24 (ASP_FSYNC), U8.24 (ASP_FSYNC), U29.10 (ASP_FSYNC)
/FSYNC_X: R249.1, U38.41 (X0D35)
/GNDPC: C280.2, C281.2, C282.2, C283.2, C284.2, J5.6, R246.2, R247.2, U43.2 (GND), U44.3 (GND1), U44.9 (EQ10), U44.10 (EQ11), U44.12 (GND1)
/HP1L_N: C232.2, J3.2, R225.2
/HP1L_P: C232.1, J3.1, R223.2
/HP1R_N: C237.2, J3.5, R229.2
/HP1R_P: C237.1, J3.4, R227.2
/HP2L_N: C242.2, J3.8, R233.2
/HP2L_P: C242.1, J3.7, R231.2
/HP2R_N: C247.2, J3.11, R237.2
/HP2R_P: C247.1, J3.10, R235.2
/HUB_DM: J4.2, U38.28 (USB_DM), U42.3 (I/O2), U42.4 (I/O2)
/HUB_DP: J4.3, U38.29 (USB_DP), U42.1 (I/O1), U42.6 (I/O1)
/HUB_VBUS: J4.1, R244.1, U42.5 (VBUS)
/HUB_VBUS_S: R244.2, R245.1, U38.46 (X0D40)
/ISO_V1: C281.1, U44.2 (V3P3V1), U44.13 (CDPENZ1)
/ISO_V18: C282.1, C283.1, C284.1, U44.4 (V1P8V1), U44.11 (V1P8V1)
/MCLK: R6.2, R8.2, R9.1, R19.1, R29.1, R198.1, R238.1, R241.1
/MCLK_ADCA: R9.2, U6.34 (MCLK)
/MCLK_ADCB: R19.2, U7.34 (MCLK)
/MCLK_ADCC: R29.2, U8.34 (MCLK)
/MCLK_DAC: R198.2, U29.8 (MCLK)
/MCLK_XA: R238.2, U38.7 (X0D11)
/MCLK_XB: R241.2, U39.7 (X0D11)
/OSC44_EN: R7.1, U38.55 (X0D31), Y2.1 (EN)
/OSC44_OUT: R8.1, Y2.3 (OUT)
/OSC48_EN: R5.1, U38.54 (X0D30), Y1.1 (EN)
/OSC48_OUT: R6.1, Y1.3 (OUT)
/PC_CC1: J5.4, R246.1
/PC_CC2: J5.5, R247.1
/PC_DM: J5.2, U43.3 (I/O2), U43.4 (I/O2), U44.7 (UD-)
/PC_DP: J5.3, U43.1 (I/O1), U43.6 (I/O1), U44.8 (UD+)
/PC_VBUS: C280.1, J5.1, U43.5 (VBUS), U44.1 (VBUS1), U44.5 (VCC1)
/PDM_CLK: J7.1, U39.9 (X1D00)
/PDM_DATA: J7.2, U39.10 (X1D01)
/PLLA: C258.1, C259.1, FB1.2, U38.22 (PLL_AVDD)
/PLLB: C274.1, C275.1, FB2.2, U39.22 (PLL_AVDD)
/QCLKA: U38.5 (X0D10), U40.6 (CLK)
/QCLKB: U39.5 (X0D10), U41.6 (CLK)
/QCSA: R240.1, U38.3 (X0D01), U40.1 (~CS)
/QCSB: R243.1, U39.3 (X0D01), U41.1 (~CS)
/QD0A: U38.59 (X0D04), U40.5 (DI/IO_{0})
/QD0B: U39.59 (X0D04), U41.5 (DI/IO_{0})
/QD1A: U38.1 (X0D05), U40.2 (DO/IO_{1})
/QD1B: U39.1 (X0D05), U41.2 (DO/IO_{1})
/QD2A: U38.60 (X0D06), U40.3 (~WP/IO_{2})
/QD2B: U39.60 (X0D06), U41.3 (~WP/IO_{2})
/QD3A: U38.2 (X0D07), U40.7 (~HOLD/~RESET/IO_{3})
/QD3B: U39.2 (X0D07), U41.7 (~HOLD/~RESET/IO_{3})
/REG_NR: C5.1, U3.14 (NR)
/RSTA: C262.1, J8.5, R239.1, U38.21 (RST_N)
/RSTB: C278.1, J9.5, R242.1, U39.21 (RST_N)
/RST_ADCA: R10.1, R11.2, U6.23 (RESET)
/RST_ADCB: R20.1, R21.2, U7.23 (RESET)
/RST_ADCC: R30.1, R31.2, U8.23 (RESET)
/RST_DAC: R199.1, R200.2, U29.5 (RESET)
/SPI_MISO: U6.35 (SPI_SDO/I2C_SCL), U7.35 (SPI_SDO/I2C_SCL), U8.35 (SPI_SDO/I2C_SCL), U29.18 (SPI_SDO/I2C_SCL), U38.13 (X1D10)
/SPI_MOSI: U6.37 (SPI_SDI/I2C_SDA), U7.37 (SPI_SDI/I2C_SDA), U8.37 (SPI_SDI/I2C_SDA), U29.19 (SPI_SDI/I2C_SDA), U38.10 (X1D01)
/SPI_SCK: R252.1, U6.36 (SPI_SCK), U7.36 (SPI_SCK), U8.36 (SPI_SCK), U29.17 (SPI_SCK), U38.9 (X1D00)
/SWA: L1.1, U4.3 (SW)
/SWB: L2.1, U5.3 (SW)
/TCKA: J8.1, U38.24 (TCK)
/TCKB: J9.1, U39.24 (TCK)
/TDIA: J8.3, U38.18 (TDI)
/TDIB: J9.3, U39.18 (TDI)
/TDOA: J8.4, U38.20 (TDO)
/TDOB: J9.4, U39.20 (TDO)
/TMSA: J8.2, U38.23 (TMS)
/TMSB: J9.2, U39.23 (TMS)
/UDM: U39.28 (USB_DM), U44.22 (DD-)
/UDP: U39.29 (USB_DP), U44.21 (DD+)
/XINA: C260.1, U38.16 (XIN), Y3.1
/XINB: C276.1, U39.16 (XIN), Y4.1
/XLA_I0: U38.35 (X1D17), U39.36 (X1D18)
/XLA_I1: U38.33 (X1D16), U39.37 (X1D19)
/XLA_O0: U38.36 (X1D18), U39.35 (X1D17)
/XLA_O1: U38.37 (X1D19), U39.33 (X1D16)
/XOUTA: C261.1, U38.15 (XOUT), Y3.3
/XOUTB: C277.1, U39.15 (XOUT), Y4.3
GND: C1.2, C2.2, C3.2, C4.2, C5.2, C6.2, C7.2, C8.2, C9.2, C10.2, C11.2, C12.2, C13.2, C14.2, C15.2, C16.2, C17.2, C18.2, C19.2, C20.2, C21.2, C22.2, C23.2, C28.2, C29.2, C30.2, C31.2, C32.2, C33.2, C34.2, C35.2, C36.2, C37.2, C38.2, C43.2, C44.2, C45.2, C46.2, C47.2, C48.2, C49.2, C50.2, C51.2, C52.2, C53.2, C56.2, C57.2, C58.2, C59.2, C65.2, C66.2, C72.2, C73.2, C79.2, C80.2, C86.2, C87.2, C93.2, C94.2, C100.2, C101.2, C107.2, C108.2, C114.2, C115.2, C121.2, C122.2, C128.2, C129.2, C135.2, C136.2, C142.2, C143.2, C149.2, C150.2, C156.2, C157.2, C163.2, C164.2, C170.2, C171.2, C177.2, C178.2, C184.2, C185.2, C191.2, C192.2, C198.2, C199.2, C200.2, C201.2, C202.2, C203.2, C204.2, C206.2, C207.2, C208.2, C209.2, C213.2, C214.2, C218.2, C219.2, C223.2, C224.2, C228.2, C229.2, C233.2, C234.2, C238.2, C239.2, C243.2, C244.2, C248.2, C249.2, C250.2, C251.2, C252.2, C253.2, C254.2, C255.2, C256.2, C257.2, C258.2, C259.2, C260.2, C261.2, C262.2, C263.2, C264.2, C265.2, C266.2, C267.2, C268.2, C269.2, C270.2, C271.2, C272.2, C273.2, C274.2, C275.2, C276.2, C277.2, C278.2, C279.2, C285.2, C286.2, C287.2, C288.2, C289.2, C290.2, C291.1, C292.2, C293.1, C294.2, D1.1 (A), D2.1 (A), D3.1 (A), D4.1 (A), D5.1 (A), D6.1 (A), D7.1 (A), D8.1 (A), D9.1 (A), D10.1 (A), D11.1 (A), D12.1 (A), D13.1 (A), D14.1 (A), D15.1 (A), D16.1 (A), D17.1 (A), D18.1 (A), D19.1 (A), D20.1 (A), D21.1 (A), D22.1 (A), D23.1 (A), D24.1 (A), D25.1 (A), D26.1 (A), D27.1 (A), D28.1 (A), D29.1 (A), D30.1 (A), D31.1 (A), D32.1 (A), D33.1 (A), D34.1 (A), D35.1 (A), D36.1 (A), D37.1 (A), D38.1 (A), D39.1 (A), D40.1 (A), J1.3, J1.4, J1.7, J1.8, J1.11, J1.12, J1.15, J1.16, J1.19, J1.20, J1.23, J1.24, J1.27, J1.28, J1.31, J1.32, J1.35, J1.36, J1.39, J1.40, J2.3, J2.4, J2.7, J2.8, J2.11, J2.12, J2.15, J2.16, J2.19, J2.20, J2.23, J2.24, J2.27, J2.28, J2.31, J2.32, J2.35, J2.36, J2.39, J2.40, J2.43, J2.44, J3.3, J3.6, J3.9, J3.12, J4.4, J6.3, J6.6, J7.4, J8.6, J9.6, R2.2, R4.2, R7.2, R10.2, R13.2, R14.2, R15.2, R16.2, R20.2, R23.2, R24.2, R25.2, R26.2, R30.2, R33.2, R34.2, R35.2, R36.2, R44.2, R45.2, R52.2, R53.2, R60.2, R61.2, R68.2, R69.2, R76.2, R77.2, R84.2, R85.2, R92.2, R93.2, R100.2, R101.2, R108.2, R109.2, R116.2, R117.2, R124.2, R125.2, R132.2, R133.2, R140.2, R141.2, R148.2, R149.2, R156.2, R157.2, R164.2, R165.2, R172.2, R173.2, R180.2, R181.2, R188.2, R189.2, R196.2, R197.2, R199.2, R202.2, R203.2, R204.2, R205.2, R245.2, R250.2, R251.2, R252.2, U1.2 (GND), U2.2 (GND), U3.7 (GND), U3.8 (1.6V), U3.11 (0.2V), U3.12 (0.1V), U3.21 (EP), U4.2 (GND), U5.2 (GND), U6.6 (GND_A), U6.8 (GND_A), U6.30 (GND_D), U6.49 (EP), U7.6 (GND_A), U7.8 (GND_A), U7.30 (GND_D), U7.49 (EP), U8.6 (GND_A), U8.8 (GND_A), U8.30 (GND_D), U8.49 (EP), U29.3 (GND_A), U29.12 (GND_D), U29.13 (ASP_DIN4/DSD_DIN4), U29.14 (ASP_DIN3/DSD_DIN3), U29.15 (ASP_DIN2/DSD_DIN2), U29.37 (GND_A), U29.49 (EP), U38.65 (VSS), U39.65 (VSS), U40.4 (GND), U41.4 (GND), U42.2 (GND), U44.17 (GND2), U44.19 (EQ21), U44.20 (EQ20), U44.26 (GND2), Y1.2 (GND), Y2.2 (GND), Y3.2 (G), Y3.4 (G), Y4.2 (G), Y4.4 (G)

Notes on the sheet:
R1 -> A1: 18 ADC pairs (8 Vrms FS), A1 -> R1: Main/Aux DAC pairs, A1 -> F1: Phones pairs; xcore A: TDM master, SPI to the converters, USB port A (hub on R2), xcore B: USB port B through the ISOUSB211 (isolated ground GNDPC)
ADC buffers x 1/4 (8 Vrms FS from R1, Cirrus circuit), DAC I-V stages (AN0679), TDM master xcore A, isolated USB port B on xcore B
Rev 0.1: schematic only; plan and pinouts in hardware/a1-digital/PLAN.md; check notes in design.py

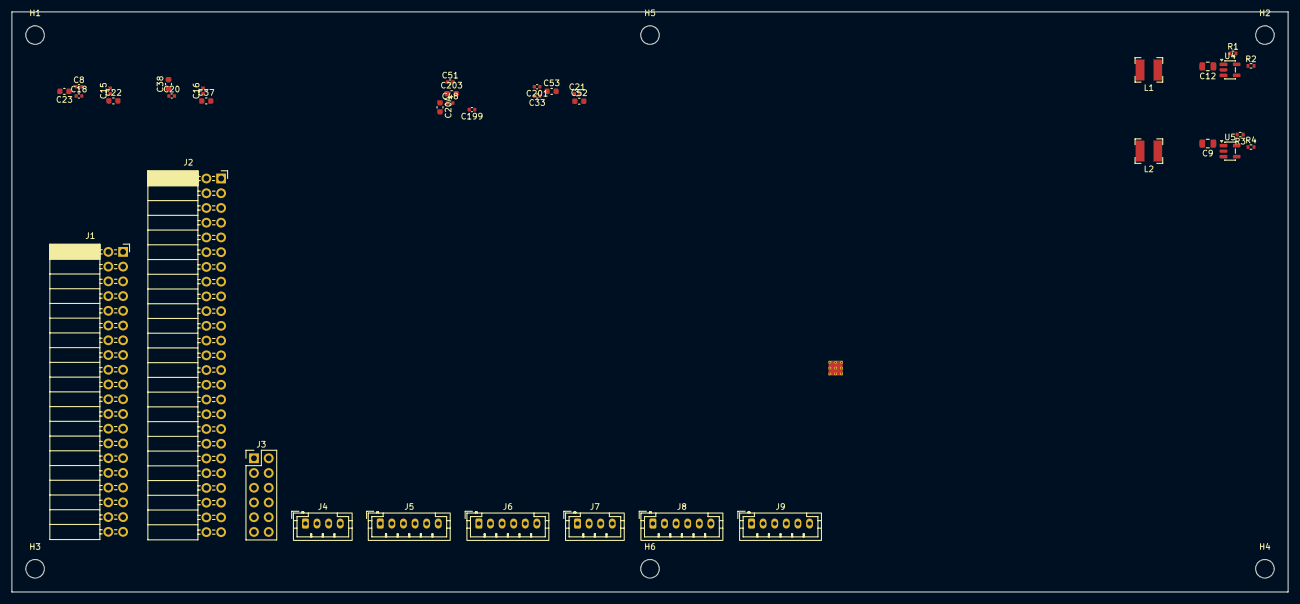
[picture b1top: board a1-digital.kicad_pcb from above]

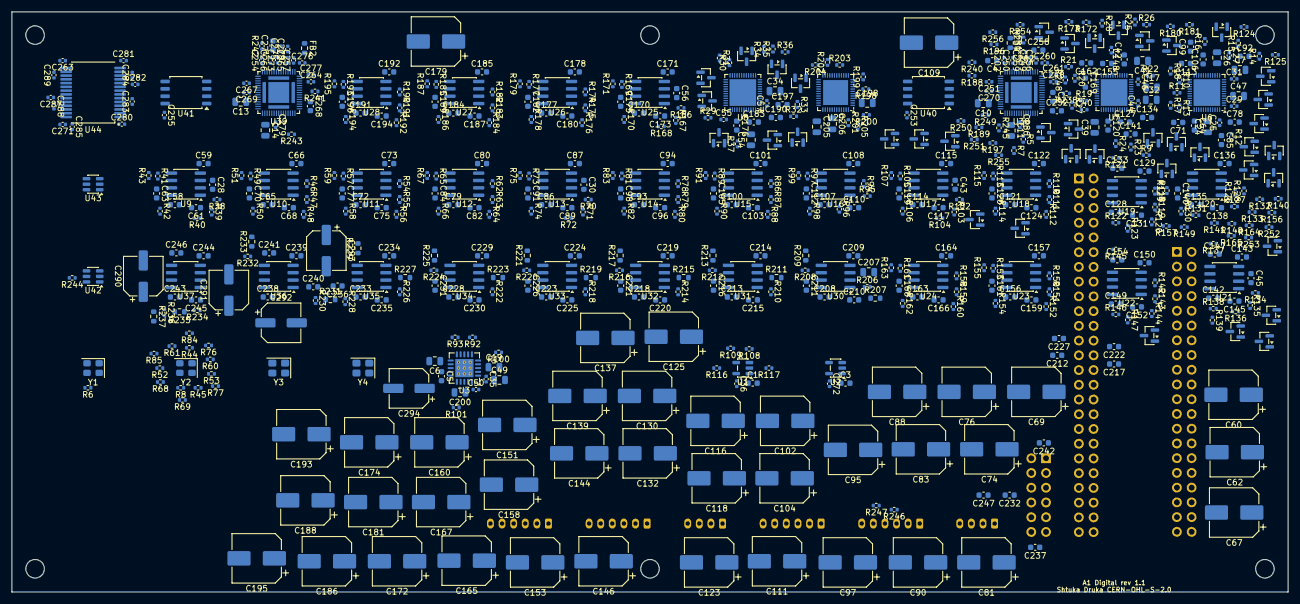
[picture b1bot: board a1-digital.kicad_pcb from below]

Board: 4 copper layers, 220.0 x 100.0 mm, 657 parts (613 on the bottom side), 387 nets, no tracks yet.

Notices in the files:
hardware/a1-digital/a1-digital.kicad_pcb:
Shtuka Druka - open hardware, CERN-OHL-S-2.0
Shtuka Druka CERN-OHL-S-2.0
